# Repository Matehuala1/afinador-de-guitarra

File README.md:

# Afinador Digital para Guitarra con MSP430

Este proyecto implementa un **afinador digital para guitarra** usando el microcontrolador **MSP430**. Detecta la frecuencia de una señal de audio (como la de una cuerda vibrante), identifica la nota más cercana entre E2, A, D, G, B y E4, y muestra si la afinación es baja (bemol), precisa o alta (sostenido) mediante LEDs.

---

##  Funcionalidades

- Lectura de señal analógica mediante uos de Hardware e interrupciones del timer.
- Cálculo de frecuencia en tiempo real.
- Comparación con notas estándar para afinación de guitarra.
- Visualización de la nota detectada en un display.
- Indicadores LED para mostrar si la nota está afinada, baja o alta.

---

## Notas Soportadas

Las notas base utilizadas están en la afinación estándar de guitarra:

| Nota | Frecuencia (Hz) |
|------|-----------------|
| E2   | 82              |
| A    | 110             |
| D    | 147             |
| G    | 196             |
| B    | 247             |
| E4   | 333             |

---

## Arquitectura del Código

- `TiposNotas`: Enumeración de notas musicales.
- `Notas`: Estructura que vincula una nota con su frecuencia.
- `tablaNotas[]`: Tabla de referencia para afinación.
- `detectarNota(f)`: Determina la nota más cercana a una frecuencia detectada.
- `indicarAfinacion(f, notaRef)`: Muestra si la cuerda está afinada, baja o alta.
- `mostrar_nota(nota)`: Visualiza la nota actual en el display.
- `TIMER0_A0_ISR`: ISR que mide la frecuencia a través de flancos de subida.

---

## Pines Utilizados (MSP430)

| Puerto | Función                          |
|--------|----------------------------------|
| P6.0   | Entrada de señal de audio        |
| P1.0   | LED indicador de lectura         |
| P2.X   | Display de nota (7 segmentos)    |
| P3.0–P3.4 | LEDs para afinación (bajo/alto/preciso) |
| P4.0   | Salida de prueba (osciloscopio)  |

---

## Cómo Funciona

1. El microcontrolador mide el período de la señal entrante mediante interrupciones del TimerA.
2. Calcula la frecuencia basada en el tiempo entre flancos.
3. Se compara la frecuencia con la tabla de notas estándar.
4. Se indica:
   - Nota detectada (en el display).
   - Estado de afinación (mediante LEDs).

---

## Requisitos

- Microcontrolador MSP430 (probado en LaunchPad MSP430G2553).
- Fuente de señal de audio (micrófono o captador piezoeléctrico).
- LEDs y display de 7 segmentos conectados a los pines indicados (PCB diseñada especificamente para esta aplicacion).

---

## Consideraciones

- El cálculo de desviación (bemol/sostenido) usa un ±6% respecto a la frecuencia de referencia.
- El código puede mejorarse usando tipos `float` para mayor precisión en comparación de afinación.
- Asegúrate de filtrar adecuadamente la señal para evitar falsas detecciones.

---

## Licencia

Este proyecto es de uso libre con fines educativos.

---

## Autor

Juan Gilberto Prado Matehuala
Jorge Eduardo Davila Garcia
Jonathan Brown Moreno
---

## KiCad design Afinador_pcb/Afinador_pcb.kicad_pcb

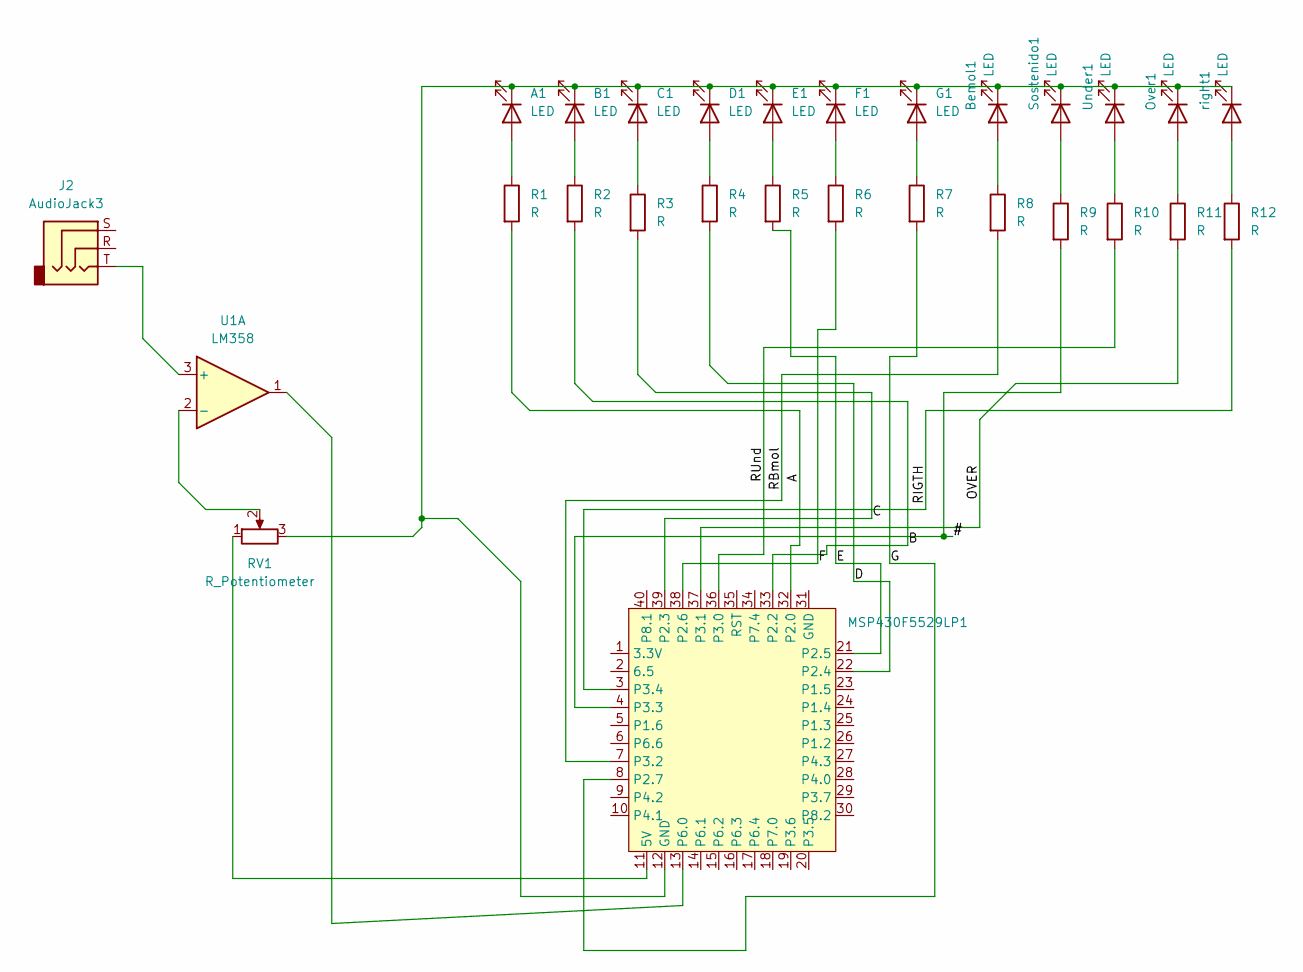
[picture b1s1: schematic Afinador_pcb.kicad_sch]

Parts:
A1: LED; LED_2512_6332Metric_Pad1.52x3.35mm_HandSolder
B1: LED; LED_2512_6332Metric_Pad1.52x3.35mm_HandSolder
Bemol1: LED; LED_1210_3225Metric_Pad1.42x2.65mm_HandSolder
C1: LED; LED_2512_6332Metric_Pad1.52x3.35mm_HandSolder
D1: LED; LED_2512_6332Metric_Pad1.52x3.35mm_HandSolder
E1: LED; LED_2512_6332Metric_Pad1.52x3.35mm_HandSolder
F1: LED; LED_2512_6332Metric_Pad1.52x3.35mm_HandSolder
G1: LED; LED_2512_6332Metric_Pad1.52x3.35mm_HandSolder
J2: AudioJack3; Jack_6.35mm_Neutrik_NMJ6HFD3_Horizontal
MSP430F5529LP1: MSP430F5529LP
Over1: LED; LED_1210_3225Metric_Pad1.42x2.65mm_HandSolder
R1, R2, R3, R4, R5, R6, R7, R8, R9, R10, R11, R12: R; R_1206_3216Metric_Pad1.30x1.75mm_HandSolder
RV1: R_Potentiometer; Potentiometer_ACP_CA14-H2,5_Horizontal
Sostenido1: LED; LED_1210_3225Metric_Pad1.42x2.65mm_HandSolder
U1: LM358; DIP-8_W7.62mm_Socket
Under1: LED; LED_1210_3225Metric_Pad1.42x2.65mm_HandSolder
right1: LED; LED_1210_3225Metric_Pad1.42x2.65mm_HandSolder

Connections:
/#: MSP430F5529LP1.4 (P3.3), R9.2
/A: MSP430F5529LP1.32 (P2.0), R1.2
/B: MSP430F5529LP1.33 (P2.2), R2.2
/C: MSP430F5529LP1.39 (P2.3), R3.2
/D: MSP430F5529LP1.22 (P2.4), R4.2
/E: MSP430F5529LP1.21 (P2.5), R5.2
/F: MSP430F5529LP1.38 (P2.6), R6.2
/G: MSP430F5529LP1.8 (P2.7), R7.2
/OVER: MSP430F5529LP1.37 (P3.1), R11.2
/RBmol: MSP430F5529LP1.7 (P3.2), R8.2
/RIGTH: MSP430F5529LP1.3 (P3.4), R12.2
/RUnd: MSP430F5529LP1.36 (P3.0), R10.2
unnamed: A1.2 (A), R1.1
unnamed: A1.1 (K), B1.1 (K), Bemol1.1 (K), C1.1 (K), D1.1 (K), E1.1 (K), F1.1 (K), G1.1 (K), MSP430F5529LP1.12 (GND), Over1.1 (K), RV1.3, Sostenido1.1 (K), Under1.1 (K), right1.1 (K)
unnamed: B1.2 (A), R2.1
unnamed: Bemol1.2 (A), R8.1
unnamed: C1.2 (A), R3.1
unnamed: D1.2 (A), R4.1
unnamed: E1.2 (A), R5.1
unnamed: F1.2 (A), R6.1
unnamed: G1.2 (A), R7.1
unnamed: MSP430F5529LP1.11 (5V), RV1.1
unnamed: MSP430F5529LP1.13 (P6.0), U1.1
unnamed: Over1.2 (A), R11.1
unnamed: R9.1, Sostenido1.2 (A)
unnamed: J2.T, U1.3 (+)
unnamed: RV1.2, U1.2 (-)
unnamed: R10.1, Under1.2 (A)
unnamed: R12.1, right1.2 (A)

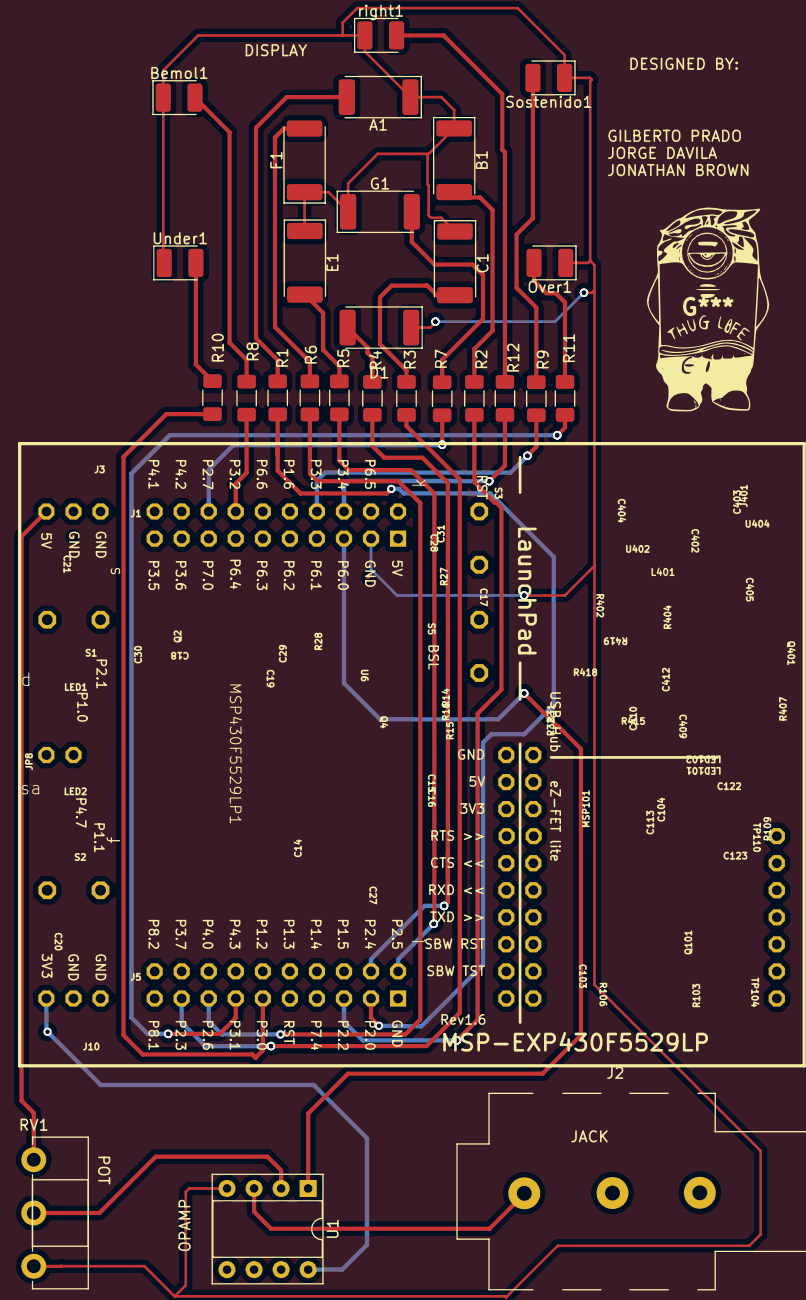
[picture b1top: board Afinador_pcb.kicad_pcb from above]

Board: 2 copper layers, 28 parts (0 on the bottom side), 29 nets.

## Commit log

2025-05-10 main 1
2025-05-10 clean_code
2025-05-10 correccion de muestra en el display
2025-05-15 Final Result
